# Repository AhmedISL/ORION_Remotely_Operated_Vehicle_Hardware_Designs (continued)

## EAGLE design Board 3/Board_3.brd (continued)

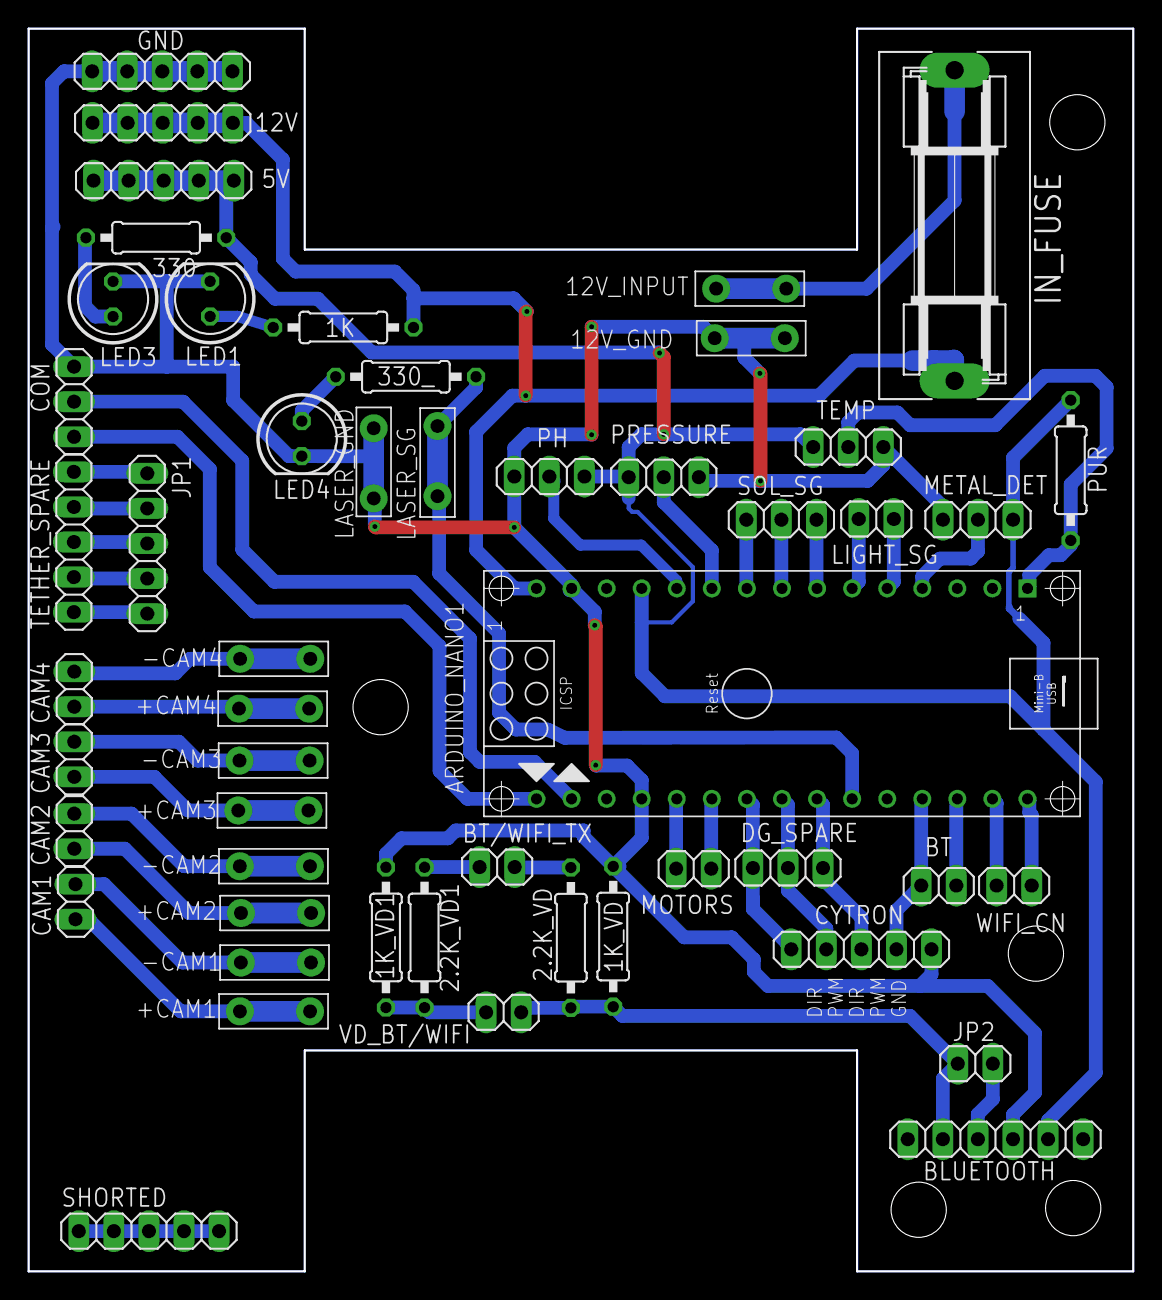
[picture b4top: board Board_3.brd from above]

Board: 2 copper layers, 80.0 x 90.0 mm, 51 parts (0 on the bottom side), 47 nets.
